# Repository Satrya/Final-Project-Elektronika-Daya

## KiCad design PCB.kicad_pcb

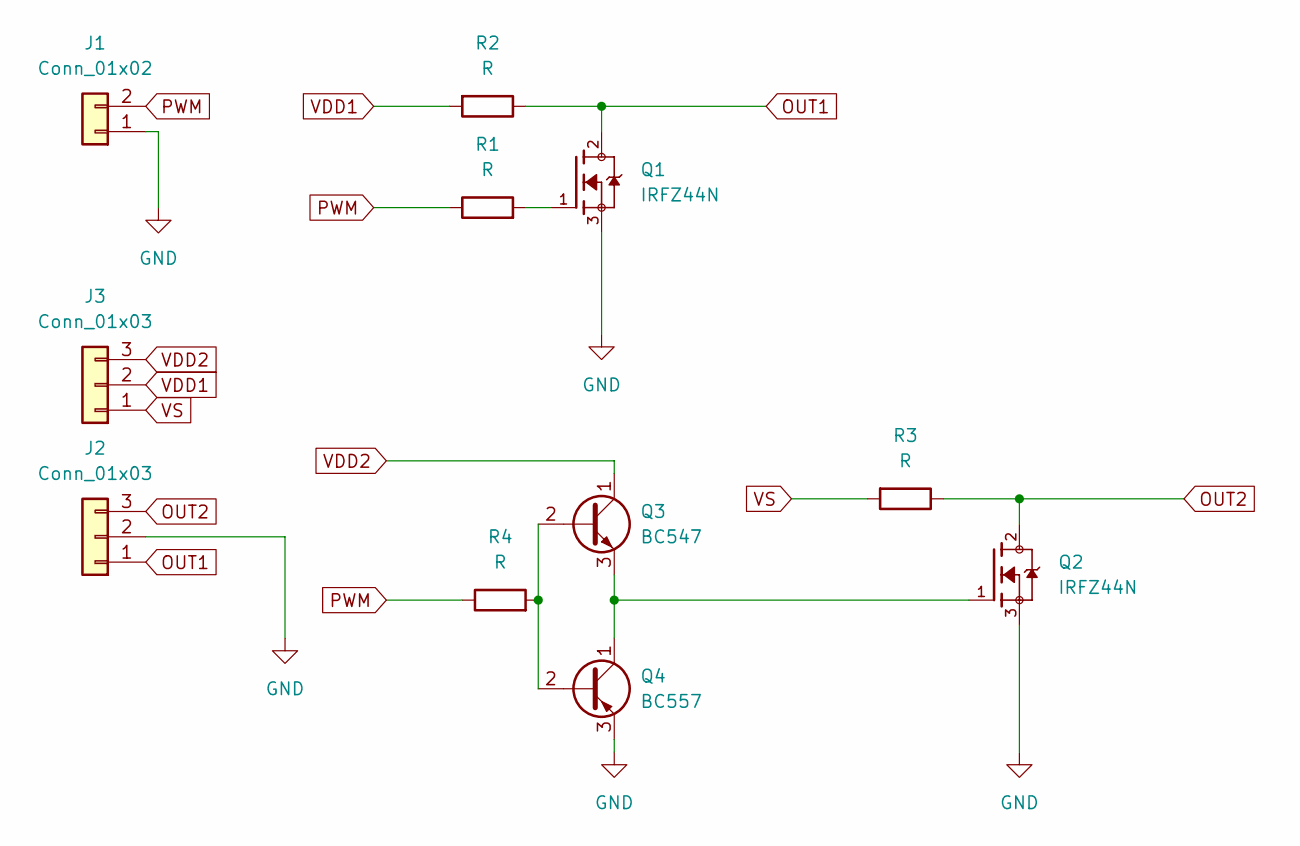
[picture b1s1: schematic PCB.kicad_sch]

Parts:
J1: Conn_01x02; PinHeader_1x02_P2.54mm_Vertical
J2, J3: Conn_01x03; PinHeader_1x03_P2.54mm_Vertical
Q1, Q2: IRFZ44N; TO254P1016X419X2286-3; PARTREV 09/21/10
Q3: BC547; TO-92_Inline
Q4: BC557; TO-92_Inline
R1, R2, R3, R4: R; R_Axial_DIN0207_L6.3mm_D2.5mm_P10.16mm_Horizontal

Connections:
GND: J1.1, J2.2, Q1.3, Q2.3, Q4.3 (E)
unnamed: Q1.1, R1.2
unnamed: Q3.2 (B), Q4.2 (B), R4.2
unnamed: Q2.1, Q3.3 (E), Q4.1 (C)
OUT1: J2.1, Q1.2, R2.1
OUT2: J2.3, Q2.2, R3.1
PWM: J1.2, R1.1, R4.1
VDD1: J3.2, R2.2
VDD2: J3.3, Q3.1 (C)
VS: J3.1, R3.2

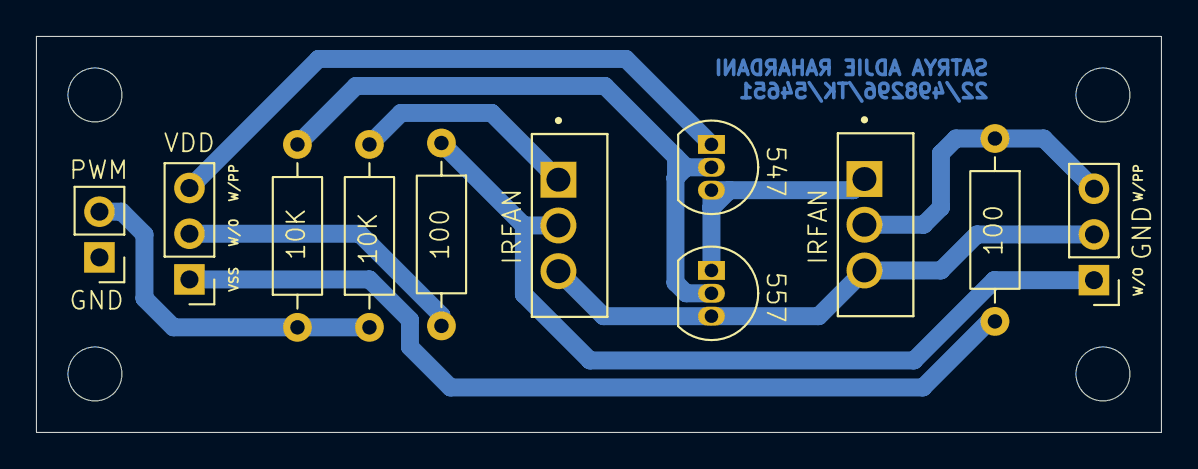
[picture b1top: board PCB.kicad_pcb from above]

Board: 2 copper layers, 62.5 x 22.0 mm, 11 parts (0 on the bottom side), 10 nets.
